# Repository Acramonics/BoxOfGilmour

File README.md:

Box Of Gilmour
==============

Andrew Martin, Acramonics, May 2025
-----------------------------------

This is my PCB for the JedsPeds 'Box of Gilmour' described at
https://www.jedspeds.co.uk/product-page/box-of-gilmour

This is a fully tested and working circuit.

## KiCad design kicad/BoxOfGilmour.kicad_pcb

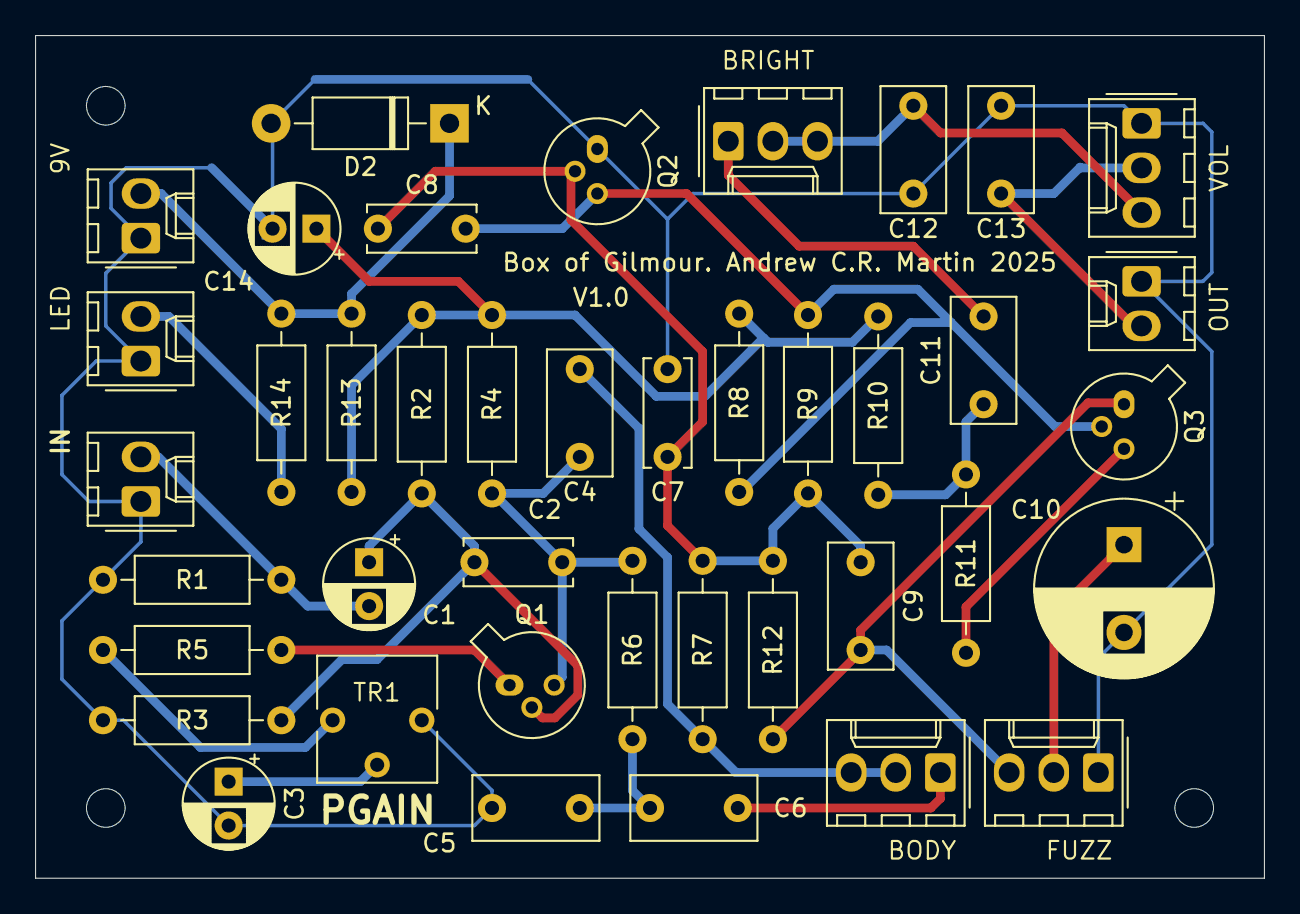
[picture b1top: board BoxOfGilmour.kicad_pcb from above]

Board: 2 copper layers, 70.0 x 48.0 mm, 41 parts (0 on the bottom side), 22 nets.

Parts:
C1: 10uF; CP_Radial_D5.0mm_P2.50mm
C2: 100pF; C_Disc_D6.0mm_W2.5mm_P5.00mm
C3: 22uF; CP_Radial_D5.0mm_P2.50mm
C4: 5.6nF; C_Rect_L7.0mm_W3.5mm_P5.00mm
C5: 4.7nF; C_Rect_L7.0mm_W3.5mm_P5.00mm
C6: 220nF; C_Rect_L7.0mm_W3.5mm_P5.00mm
C7: 470pF; C_Disc_D6.0mm_W2.5mm_P5.00mm
C8: 220pF; C_Disc_D6.0mm_W2.5mm_P5.00mm
C9: 220pF; C_Rect_L7.0mm_W3.5mm_P5.00mm
C10: 220uF; CP_Radial_D10.0mm_P5.00mm
C11: 15nF; C_Rect_L7.0mm_W3.5mm_P5.00mm
C12: 3.3nF; C_Rect_L7.0mm_W3.5mm_P5.00mm
C13: 2.2nF; C_Rect_L7.0mm_W3.5mm_P5.00mm
C14: 100uF; CP_Radial_D5.0mm_P2.50mm
D2: 1N4001; D_DO-41_SOD81_P10.16mm_Horizontal
J1, J2, J3, J4: Conn_01x03_Pin; Molex_KK-254_AE-6410-03A_1x03_P2.54mm_Vertical
J5, J6, J7, J10: Conn_01x02_Pin; Molex_KK-254_AE-6410-02A_1x02_P2.54mm_Vertical
Q1, Q2, Q3: BC109; TO-18-3
R1: 1M; R_Axial_DIN0207_L6.3mm_D2.5mm_P10.16mm_Horizontal
R2: 270K; R_Axial_DIN0207_L6.3mm_D2.5mm_P10.16mm_Horizontal
R3, R9: 100K; R_Axial_DIN0207_L6.3mm_D2.5mm_P10.16mm_Horizontal
R4, R11: 10K; R_Axial_DIN0207_L6.3mm_D2.5mm_P10.16mm_Horizontal
R5, R7, R13: 100R; R_Axial_DIN0207_L6.3mm_D2.5mm_P10.16mm_Horizontal
R6: 820R; R_Axial_DIN0207_L6.3mm_D2.5mm_P10.16mm_Horizontal
R8, R12: 56K; R_Axial_DIN0207_L6.3mm_D2.5mm_P10.16mm_Horizontal
R10: 2K7; R_Axial_DIN0207_L6.3mm_D2.5mm_P10.16mm_Horizontal
R14: R; R_Axial_DIN0207_L6.3mm_D2.5mm_P10.16mm_Horizontal
TR1(PGAIN)1: 2K; Potentiometer_Vishay_T73YP_Vertical

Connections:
+9V: D2.1 (K), J10.2, R13.1, R14.1
Earth: C3.2, C5.1, C7.2, C10.2, C12.2, C13.2, C14.2, D2.2 (A), J3.1, J4.1, J5.1, J6.1, J7.1, J10.1, Q2.1 (E), R1.2, R3.2, TR1(PGAIN)1.3
unnamed: C3.1, TR1(PGAIN)1.2
unnamed: C5.2, C6.1, R6.2
unnamed: C11.1, R10.2, R11.1
unnamed: C14.1, R2.1, R4.1, R8.2, R10.1, R13.2
unnamed: C6.2, J1.1
unnamed: C4.2, J1.2, J1.3, R7.1
unnamed: C11.2, J2.1
unnamed: C12.1, J2.2, J2.3, J4.3
unnamed: C10.1, J3.2
unnamed: C9.2, J3.3, Q3.1 (E), R12.2
unnamed: C13.1, J4.2, J7.2
unnamed: J5.2, R14.2
unnamed: C1.2, J6.2, R1.1
unnamed: C1.1, C2.1, Q1.2 (B), R2.2, R3.1
unnamed: C2.2, C4.1, Q1.3 (C), R4.2, R6.1
unnamed: Q1.1 (E), R5.1
unnamed: C7.1, C8.1, C9.1, Q2.2 (B), R7.2, R9.1, R12.1
unnamed: C8.2, Q2.3 (C), Q3.2 (B), R8.1, R9.2
unnamed: Q3.3 (C), R11.2
unnamed: R5.2, TR1(PGAIN)1.1

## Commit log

2026-01-29 Initial commit of fully working and tested version
